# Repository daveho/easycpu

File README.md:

# Easy 8 bit CPU

This is a design for an 8 bit CPU built from 74HC logic chips.

It is totally just for fun.  I may try to complete it at some point but for now it's only at the idea stage.

The [design](design) directory has a block diagram that is probably the most useful document for explaining how the CPU is intended to work.

One potentially useful component that is (probably) ready for use is a passive backplane design, which is in the [backplane2](backplane2) directory.

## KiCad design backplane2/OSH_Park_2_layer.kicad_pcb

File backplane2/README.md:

# Backplane

This is a passive backplane for projects (such as 8 bit micros and
TTL CPUs) where there are lots of parallel bus connections that
would be a pain to wire on breadboards.

The idea is that the project can be built incrementally, with
circuit modules prototyped on a small number of breadboards, and
then permanantly constructed and attached to the backplane.

The eventual finished system then uses the backplane to allow
the various circuit modules to communicate.

Kicad template from <https://github.com/Squantor/templates_kicad/tree/master/OSH_Park_2_layer>

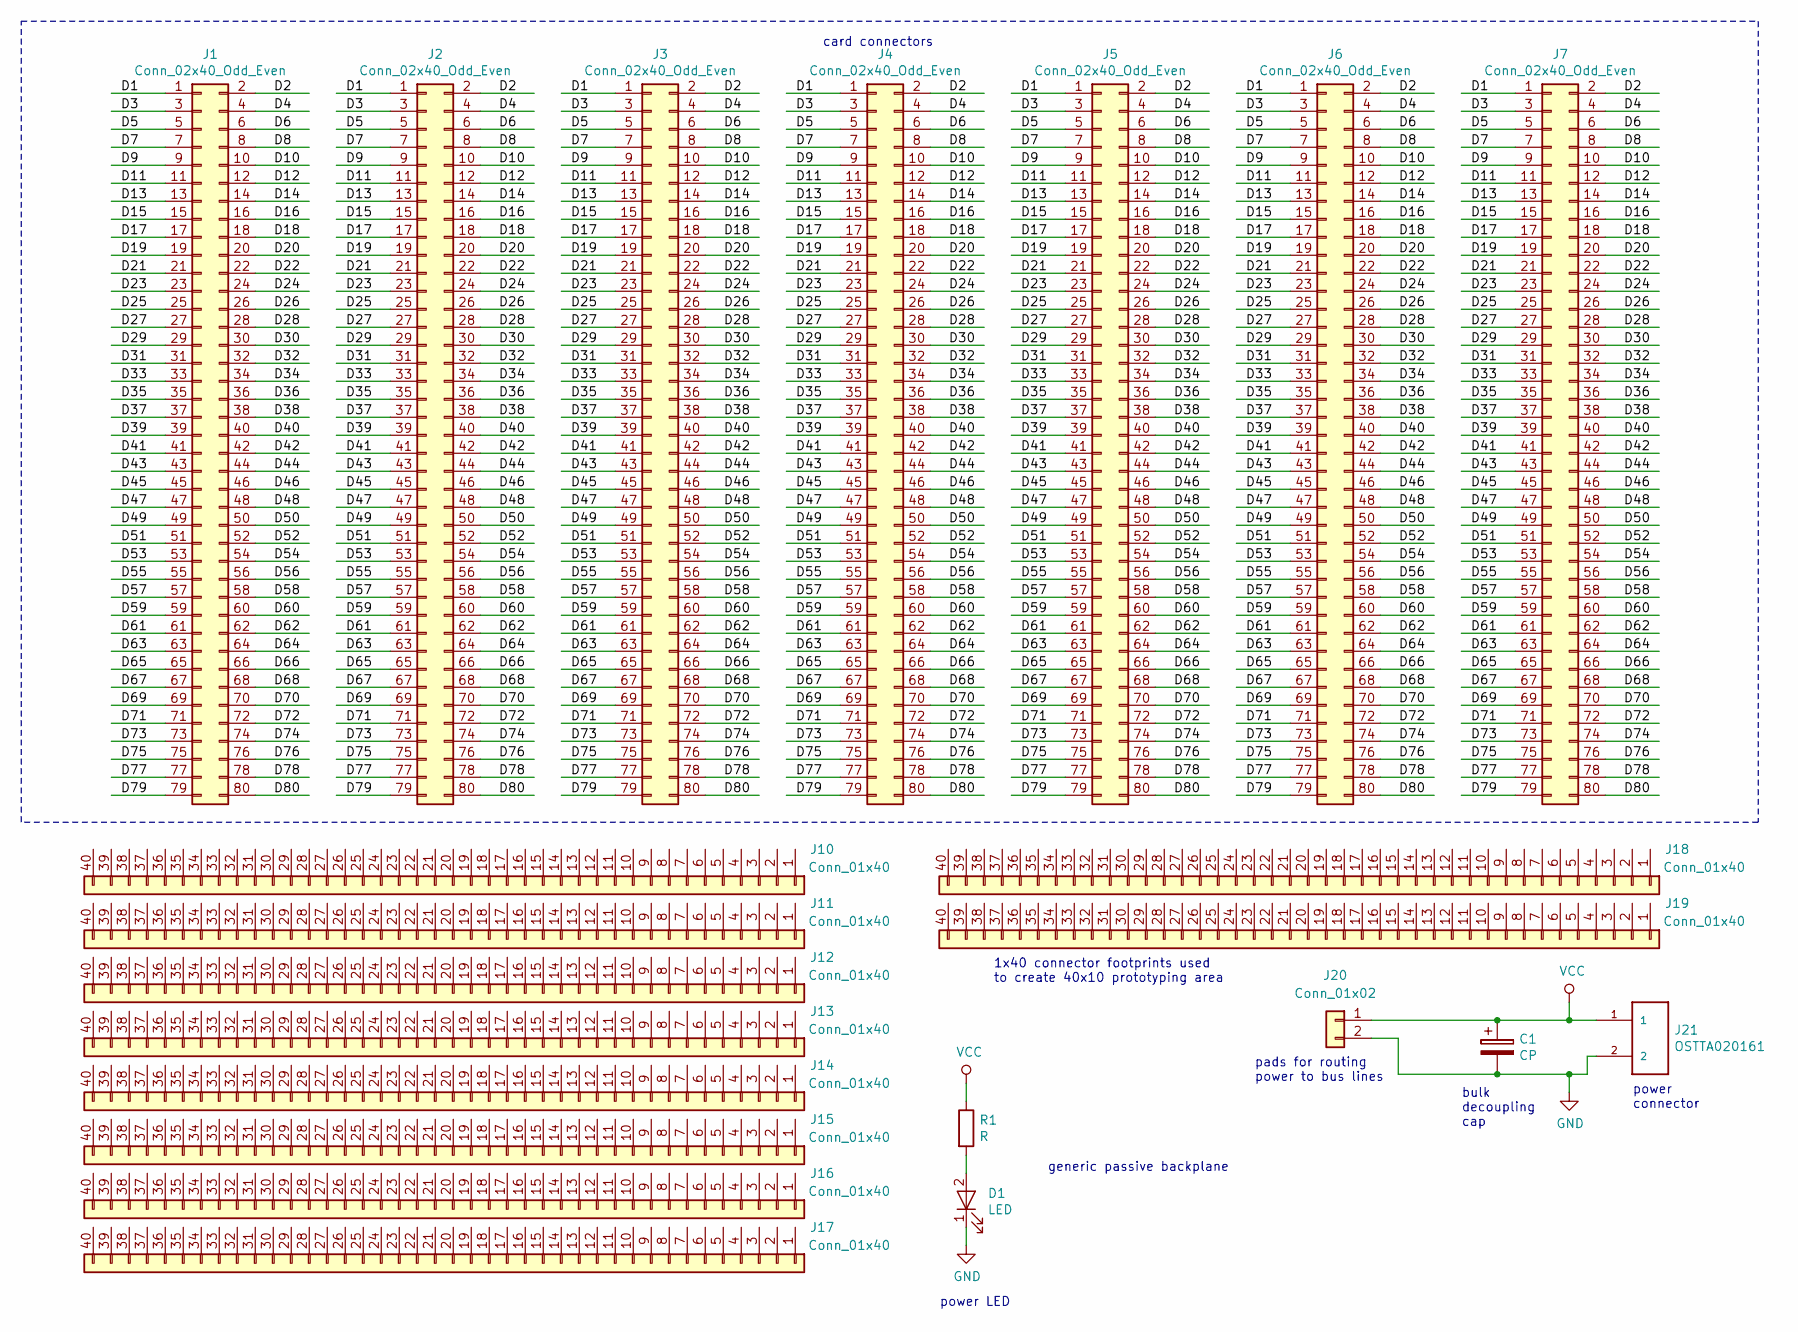
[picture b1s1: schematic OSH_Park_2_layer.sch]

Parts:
C1: CP; CP_Radial_D8.0mm_P2.50mm
D1: LED; LED_D5.0mm
J1, J2, J3, J4, J5, J6, J7: Conn_02x40_Odd_Even; PinHeader_2x40_P2.54mm_Vertical
J10, J11, J12, J13, J14, J15, J16, J17, J18, J19: Conn_01x40; PinHeader_1x40_P2.54mm_Vertical
J20: Conn_01x02; PinHeader_1x02_P2.54mm_Vertical
J21: OSTTA020161; OST_OSTTA020161
R1: R; R_Axial_DIN0204_L3.6mm_D1.6mm_P7.62mm_Horizontal

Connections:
/D1: J1.1, J2.1, J3.1, J4.1, J5.1, J6.1, J7.1
/D2: J1.2, J2.2, J3.2, J4.2, J5.2, J6.2, J7.2
/D3: J1.3, J2.3, J3.3, J4.3, J5.3, J6.3, J7.3
/D4: J1.4, J2.4, J3.4, J4.4, J5.4, J6.4, J7.4
/D5: J1.5, J2.5, J3.5, J4.5, J5.5, J6.5, J7.5
/D6: J1.6, J2.6, J3.6, J4.6, J5.6, J6.6, J7.6
/D7: J1.7, J2.7, J3.7, J4.7, J5.7, J6.7, J7.7
/D8: J1.8, J2.8, J3.8, J4.8, J5.8, J6.8, J7.8
/D9: J1.9, J2.9, J3.9, J4.9, J5.9, J6.9, J7.9
/D10: J1.10, J2.10, J3.10, J4.10, J5.10, J6.10, J7.10
/D11: J1.11, J2.11, J3.11, J4.11, J5.11, J6.11, J7.11
/D12: J1.12, J2.12, J3.12, J4.12, J5.12, J6.12, J7.12
/D13: J1.13, J2.13, J3.13, J4.13, J5.13, J6.13, J7.13
/D14: J1.14, J2.14, J3.14, J4.14, J5.14, J6.14, J7.14
/D15: J1.15, J2.15, J3.15, J4.15, J5.15, J6.15, J7.15
/D16: J1.16, J2.16, J3.16, J4.16, J5.16, J6.16, J7.16
/D17: J1.17, J2.17, J3.17, J4.17, J5.17, J6.17, J7.17
/D18: J1.18, J2.18, J3.18, J4.18, J5.18, J6.18, J7.18
/D19: J1.19, J2.19, J3.19, J4.19, J5.19, J6.19, J7.19
/D20: J1.20, J2.20, J3.20, J4.20, J5.20, J6.20, J7.20
/D21: J1.21, J2.21, J3.21, J4.21, J5.21, J6.21, J7.21
/D22: J1.22, J2.22, J3.22, J4.22, J5.22, J6.22, J7.22
/D23: J1.23, J2.23, J3.23, J4.23, J5.23, J6.23, J7.23
/D24: J1.24, J2.24, J3.24, J4.24, J5.24, J6.24, J7.24
/D25: J1.25, J2.25, J3.25, J4.25, J5.25, J6.25, J7.25
/D26: J1.26, J2.26, J3.26, J4.26, J5.26, J6.26, J7.26
/D27: J1.27, J2.27, J3.27, J4.27, J5.27, J6.27, J7.27
/D28: J1.28, J2.28, J3.28, J4.28, J5.28, J6.28, J7.28
/D29: J1.29, J2.29, J3.29, J4.29, J5.29, J6.29, J7.29
/D30: J1.30, J2.30, J3.30, J4.30, J5.30, J6.30, J7.30
/D31: J1.31, J2.31, J3.31, J4.31, J5.31, J6.31, J7.31
/D32: J1.32, J2.32, J3.32, J4.32, J5.32, J6.32, J7.32
/D33: J1.33, J2.33, J3.33, J4.33, J5.33, J6.33, J7.33
/D34: J1.34, J2.34, J3.34, J4.34, J5.34, J6.34, J7.34
/D35: J1.35, J2.35, J3.35, J4.35, J5.35, J6.35, J7.35
/D36: J1.36, J2.36, J3.36, J4.36, J5.36, J6.36, J7.36
/D37: J1.37, J2.37, J3.37, J4.37, J5.37, J6.37, J7.37
/D38: J1.38, J2.38, J3.38, J4.38, J5.38, J6.38, J7.38
/D39: J1.39, J2.39, J3.39, J4.39, J5.39, J6.39, J7.39
/D40: J1.40, J2.40, J3.40, J4.40, J5.40, J6.40, J7.40
/D41: J1.41, J2.41, J3.41, J4.41, J5.41, J6.41, J7.41
/D42: J1.42, J2.42, J3.42, J4.42, J5.42, J6.42, J7.42
/D43: J1.43, J2.43, J3.43, J4.43, J5.43, J6.43, J7.43
/D44: J1.44, J2.44, J3.44, J4.44, J5.44, J6.44, J7.44
/D45: J1.45, J2.45, J3.45, J4.45, J5.45, J6.45, J7.45
/D46: J1.46, J2.46, J3.46, J4.46, J5.46, J6.46, J7.46
/D47: J1.47, J2.47, J3.47, J4.47, J5.47, J6.47, J7.47
/D48: J1.48, J2.48, J3.48, J4.48, J5.48, J6.48, J7.48
/D49: J1.49, J2.49, J3.49, J4.49, J5.49, J6.49, J7.49
/D50: J1.50, J2.50, J3.50, J4.50, J5.50, J6.50, J7.50
/D51: J1.51, J2.51, J3.51, J4.51, J5.51, J6.51, J7.51
/D52: J1.52, J2.52, J3.52, J4.52, J5.52, J6.52, J7.52
/D53: J1.53, J2.53, J3.53, J4.53, J5.53, J6.53, J7.53
/D54: J1.54, J2.54, J3.54, J4.54, J5.54, J6.54, J7.54
/D55: J1.55, J2.55, J3.55, J4.55, J5.55, J6.55, J7.55
/D56: J1.56, J2.56, J3.56, J4.56, J5.56, J6.56, J7.56
/D57: J1.57, J2.57, J3.57, J4.57, J5.57, J6.57, J7.57
/D58: J1.58, J2.58, J3.58, J4.58, J5.58, J6.58, J7.58
/D59: J1.59, J2.59, J3.59, J4.59, J5.59, J6.59, J7.59
/D60: J1.60, J2.60, J3.60, J4.60, J5.60, J6.60, J7.60
/D61: J1.61, J2.61, J3.61, J4.61, J5.61, J6.61, J7.61
/D62: J1.62, J2.62, J3.62, J4.62, J5.62, J6.62, J7.62
/D63: J1.63, J2.63, J3.63, J4.63, J5.63, J6.63, J7.63
/D64: J1.64, J2.64, J3.64, J4.64, J5.64, J6.64, J7.64
/D65: J1.65, J2.65, J3.65, J4.65, J5.65, J6.65, J7.65
/D66: J1.66, J2.66, J3.66, J4.66, J5.66, J6.66, J7.66
/D67: J1.67, J2.67, J3.67, J4.67, J5.67, J6.67, J7.67
/D68: J1.68, J2.68, J3.68, J4.68, J5.68, J6.68, J7.68
/D69: J1.69, J2.69, J3.69, J4.69, J5.69, J6.69, J7.69
/D70: J1.70, J2.70, J3.70, J4.70, J5.70, J6.70, J7.70
/D71: J1.71, J2.71, J3.71, J4.71, J5.71, J6.71, J7.71
/D72: J1.72, J2.72, J3.72, J4.72, J5.72, J6.72, J7.72
/D73: J1.73, J2.73, J3.73, J4.73, J5.73, J6.73, J7.73
/D74: J1.74, J2.74, J3.74, J4.74, J5.74, J6.74, J7.74
/D75: J1.75, J2.75, J3.75, J4.75, J5.75, J6.75, J7.75
/D76: J1.76, J2.76, J3.76, J4.76, J5.76, J6.76, J7.76
/D77: J1.77, J2.77, J3.77, J4.77, J5.77, J6.77, J7.77
/D78: J1.78, J2.78, J3.78, J4.78, J5.78, J6.78, J7.78
/D79: J1.79, J2.79, J3.79, J4.79, J5.79, J6.79, J7.79
/D80: J1.80, J2.80, J3.80, J4.80, J5.80, J6.80, J7.80
GND: C1.2, D1.1 (K), J20.2, J21.2
unnamed: D1.2 (A), R1.2
VCC: C1.1, J20.1, J21.1, R1.1

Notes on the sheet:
card connectors
1x40 connector footprints used to create 40x10 prototyping area
power connector
generic passive backplane
pads for routing power to bus lines
bulk decoupling cap
power LED

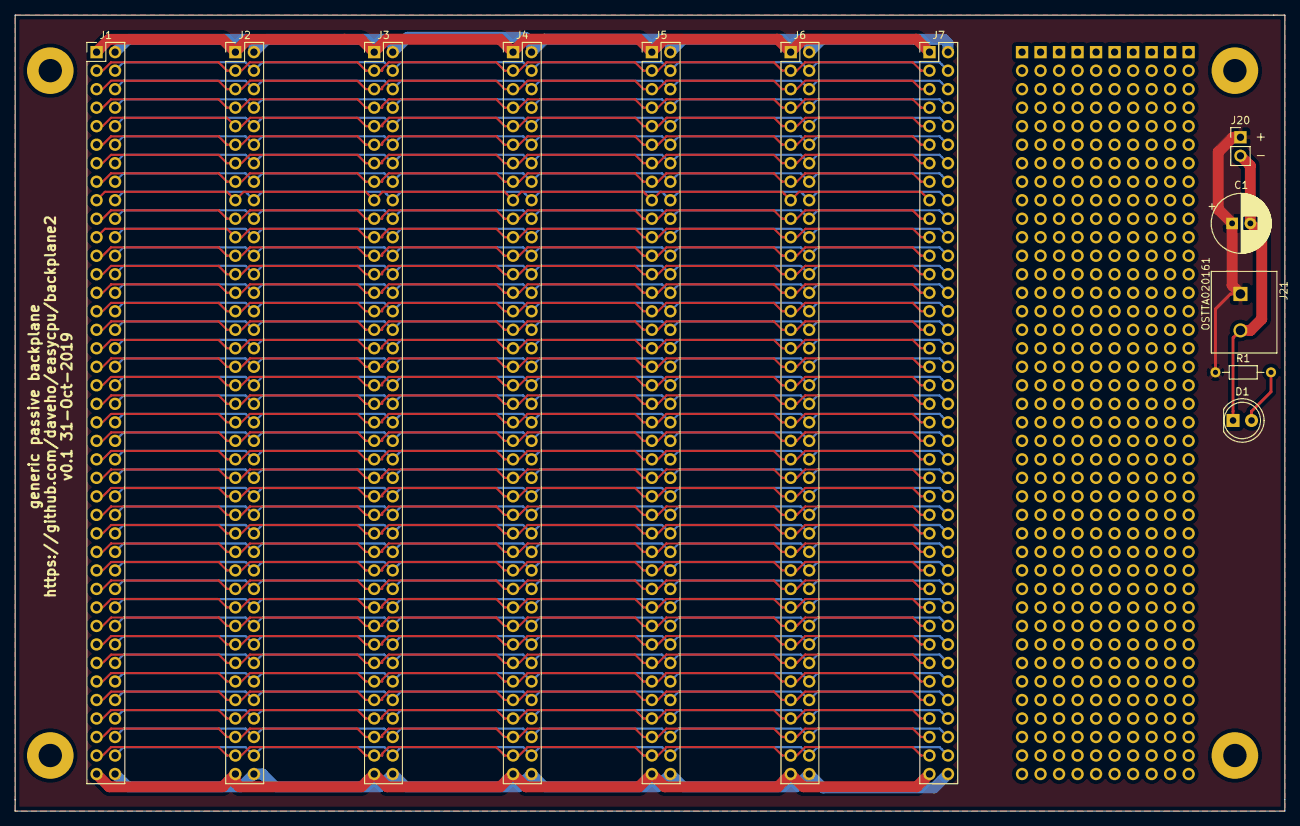
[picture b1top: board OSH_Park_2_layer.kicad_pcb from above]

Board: 2 copper layers, 174.2 x 109.2 mm, 23 parts (0 on the bottom side), 83 nets.

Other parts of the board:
N2: 20190704; Label_version

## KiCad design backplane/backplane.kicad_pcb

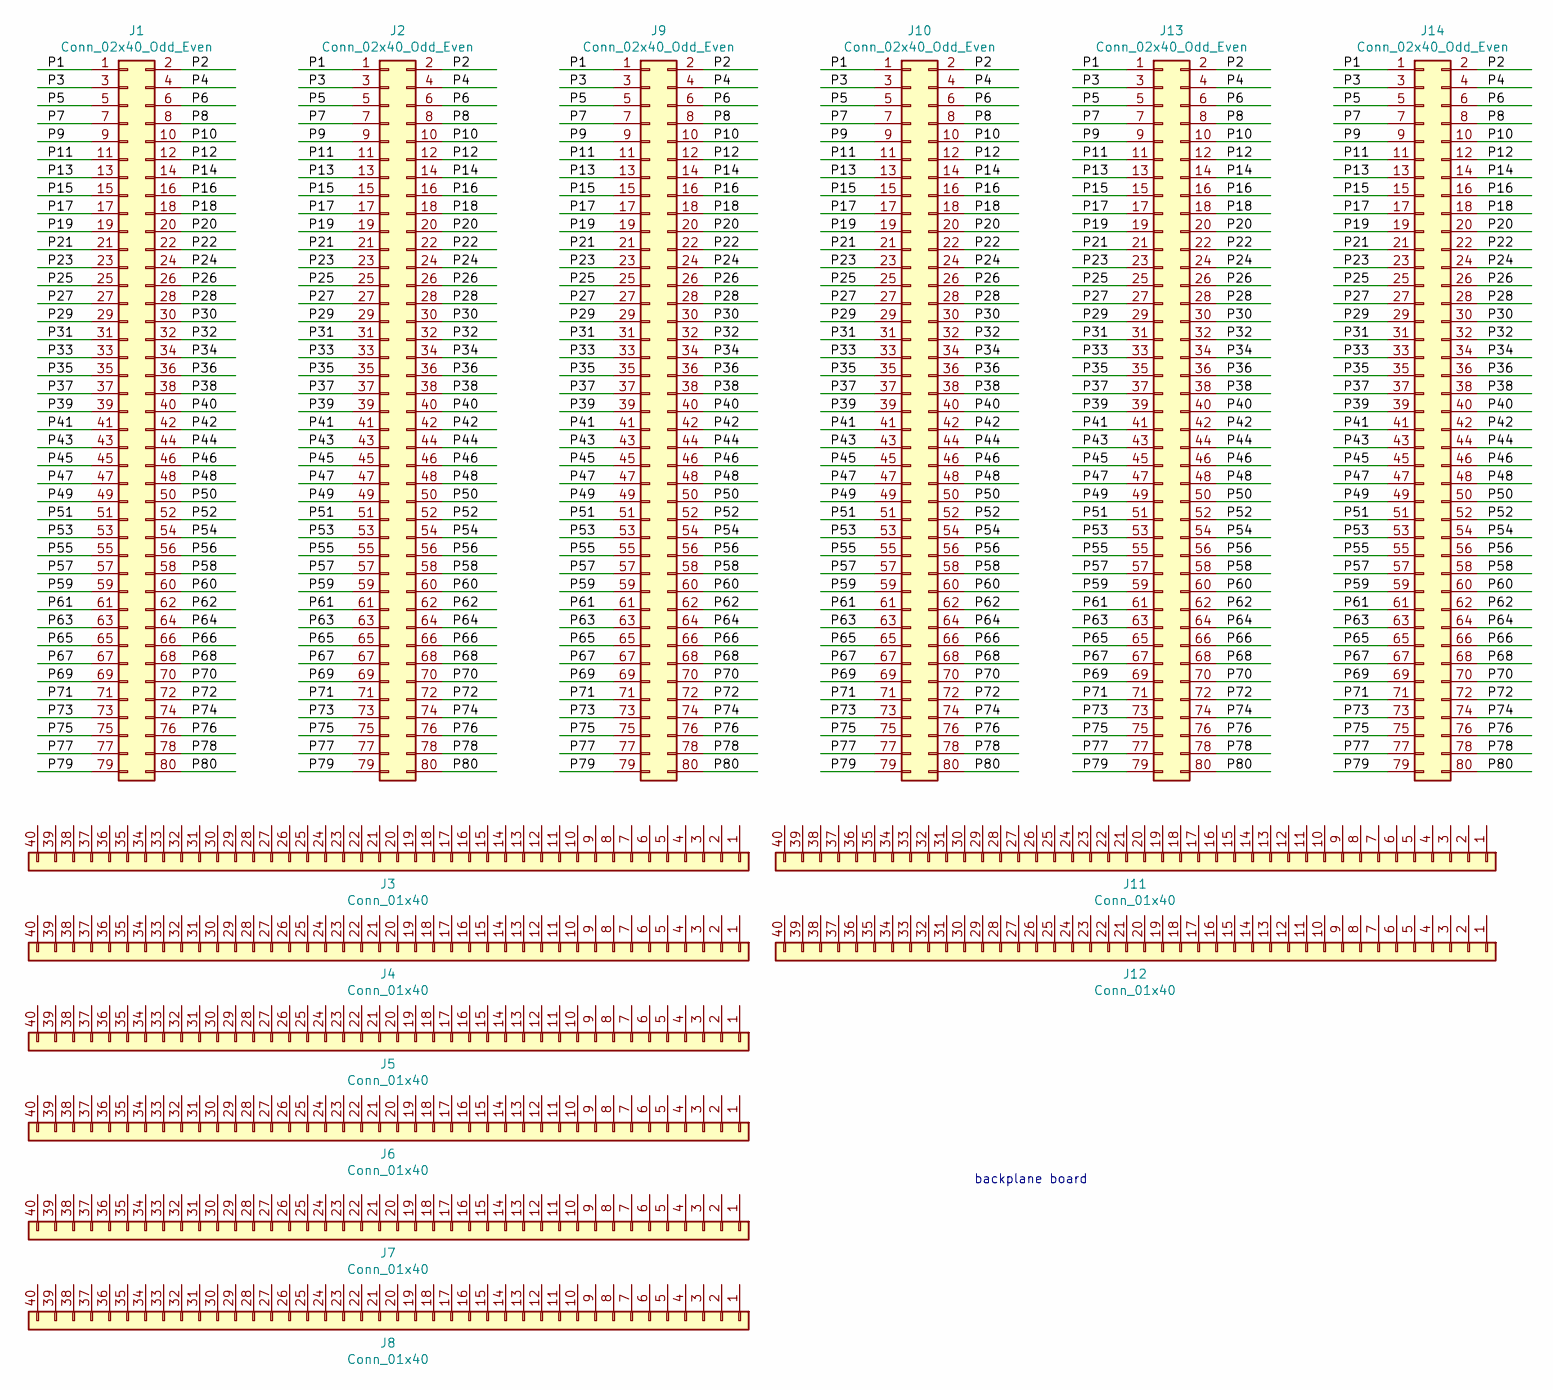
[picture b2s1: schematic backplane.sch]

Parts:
J1, J2, J9, J10, J13, J14: Conn_02x40_Odd_Even; Pin_Header_Straight_2x40_Pitch2.54mm
J3, J4, J5, J6, J7, J8, J11, J12: Conn_01x40; Pin_Header_Straight_1x40_Pitch2.54mm

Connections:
/P1: J1.1, J2.1, J9.1, J10.1, J13.1, J14.1
/P2: J1.2, J2.2, J9.2, J10.2, J13.2, J14.2
/P3: J1.3, J2.3, J9.3, J10.3, J13.3, J14.3
/P4: J1.4, J2.4, J9.4, J10.4, J13.4, J14.4
/P5: J1.5, J2.5, J9.5, J10.5, J13.5, J14.5
/P6: J1.6, J2.6, J9.6, J10.6, J13.6, J14.6
/P7: J1.7, J2.7, J9.7, J10.7, J13.7, J14.7
/P8: J1.8, J2.8, J9.8, J10.8, J13.8, J14.8
/P9: J1.9, J2.9, J9.9, J10.9, J13.9, J14.9
/P10: J1.10, J2.10, J9.10, J10.10, J13.10, J14.10
/P11: J1.11, J2.11, J9.11, J10.11, J13.11, J14.11
/P12: J1.12, J2.12, J9.12, J10.12, J13.12, J14.12
/P13: J1.13, J2.13, J9.13, J10.13, J13.13, J14.13
/P14: J1.14, J2.14, J9.14, J10.14, J13.14, J14.14
/P15: J1.15, J2.15, J9.15, J10.15, J13.15, J14.15
/P16: J1.16, J2.16, J9.16, J10.16, J13.16, J14.16
/P17: J1.17, J2.17, J9.17, J10.17, J13.17, J14.17
/P18: J1.18, J2.18, J9.18, J10.18, J13.18, J14.18
/P19: J1.19, J2.19, J9.19, J10.19, J13.19, J14.19
/P20: J1.20, J2.20, J9.20, J10.20, J13.20, J14.20
/P21: J1.21, J2.21, J9.21, J10.21, J13.21, J14.21
/P22: J1.22, J2.22, J9.22, J10.22, J13.22, J14.22
/P23: J1.23, J2.23, J9.23, J10.23, J13.23, J14.23
/P24: J1.24, J2.24, J9.24, J10.24, J13.24, J14.24
/P25: J1.25, J2.25, J9.25, J10.25, J13.25, J14.25
/P26: J1.26, J2.26, J9.26, J10.26, J13.26, J14.26
/P27: J1.27, J2.27, J9.27, J10.27, J13.27, J14.27
/P28: J1.28, J2.28, J9.28, J10.28, J13.28, J14.28
/P29: J1.29, J2.29, J9.29, J10.29, J13.29, J14.29
/P30: J1.30, J2.30, J9.30, J10.30, J13.30, J14.30
/P31: J1.31, J2.31, J9.31, J10.31, J13.31, J14.31
/P32: J1.32, J2.32, J9.32, J10.32, J13.32, J14.32
/P33: J1.33, J2.33, J9.33, J10.33, J13.33, J14.33
/P34: J1.34, J2.34, J9.34, J10.34, J13.34, J14.34
/P35: J1.35, J2.35, J9.35, J10.35, J13.35, J14.35
/P36: J1.36, J2.36, J9.36, J10.36, J13.36, J14.36
/P37: J1.37, J2.37, J9.37, J10.37, J13.37, J14.37
/P38: J1.38, J2.38, J9.38, J10.38, J13.38, J14.38
/P39: J1.39, J2.39, J9.39, J10.39, J13.39, J14.39
/P40: J1.40, J2.40, J9.40, J10.40, J13.40, J14.40
/P41: J1.41, J2.41, J9.41, J10.41, J13.41, J14.41
/P42: J1.42, J2.42, J9.42, J10.42, J13.42, J14.42
/P43: J1.43, J2.43, J9.43, J10.43, J13.43, J14.43
/P44: J1.44, J2.44, J9.44, J10.44, J13.44, J14.44
/P45: J1.45, J2.45, J9.45, J10.45, J13.45, J14.45
/P46: J1.46, J2.46, J9.46, J10.46, J13.46, J14.46
/P47: J1.47, J2.47, J9.47, J10.47, J13.47, J14.47
/P48: J1.48, J2.48, J9.48, J10.48, J13.48, J14.48
/P49: J1.49, J2.49, J9.49, J10.49, J13.49, J14.49
/P50: J1.50, J2.50, J9.50, J10.50, J13.50, J14.50
/P51: J1.51, J2.51, J9.51, J10.51, J13.51, J14.51
/P52: J1.52, J2.52, J9.52, J10.52, J13.52, J14.52
/P53: J1.53, J2.53, J9.53, J10.53, J13.53, J14.53
/P54: J1.54, J2.54, J9.54, J10.54, J13.54, J14.54
/P55: J1.55, J2.55, J9.55, J10.55, J13.55, J14.55
/P56: J1.56, J2.56, J9.56, J10.56, J13.56, J14.56
/P57: J1.57, J2.57, J9.57, J10.57, J13.57, J14.57
/P58: J1.58, J2.58, J9.58, J10.58, J13.58, J14.58
/P59: J1.59, J2.59, J9.59, J10.59, J13.59, J14.59
/P60: J1.60, J2.60, J9.60, J10.60, J13.60, J14.60
/P61: J1.61, J2.61, J9.61, J10.61, J13.61, J14.61
/P62: J1.62, J2.62, J9.62, J10.62, J13.62, J14.62
/P63: J1.63, J2.63, J9.63, J10.63, J13.63, J14.63
/P64: J1.64, J2.64, J9.64, J10.64, J13.64, J14.64
/P65: J1.65, J2.65, J9.65, J10.65, J13.65, J14.65
/P66: J1.66, J2.66, J9.66, J10.66, J13.66, J14.66
/P67: J1.67, J2.67, J9.67, J10.67, J13.67, J14.67
/P68: J1.68, J2.68, J9.68, J10.68, J13.68, J14.68
/P69: J1.69, J2.69, J9.69, J10.69, J13.69, J14.69
/P70: J1.70, J2.70, J9.70, J10.70, J13.70, J14.70
/P71: J1.71, J2.71, J9.71, J10.71, J13.71, J14.71
/P72: J1.72, J2.72, J9.72, J10.72, J13.72, J14.72
/P73: J1.73, J2.73, J9.73, J10.73, J13.73, J14.73
/P74: J1.74, J2.74, J9.74, J10.74, J13.74, J14.74
/P75: J1.75, J2.75, J9.75, J10.75, J13.75, J14.75
/P76: J1.76, J2.76, J9.76, J10.76, J13.76, J14.76
/P77: J1.77, J2.77, J9.77, J10.77, J13.77, J14.77
/P78: J1.78, J2.78, J9.78, J10.78, J13.78, J14.78
/P79: J1.79, J2.79, J9.79, J10.79, J13.79, J14.79
/P80: J1.80, J2.80, J9.80, J10.80, J13.80, J14.80

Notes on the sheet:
backplane board

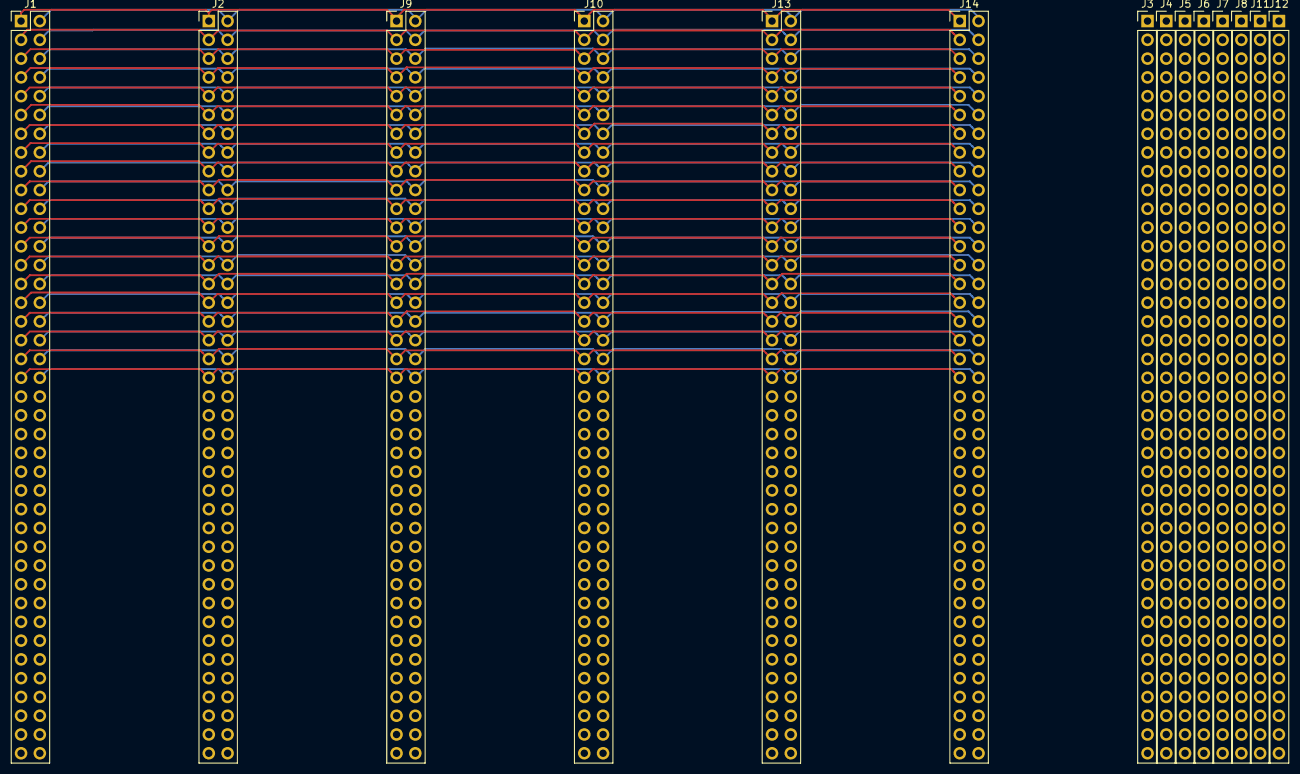
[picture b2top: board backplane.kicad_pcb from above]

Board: 2 copper layers, 14 parts (0 on the bottom side), 80 nets.

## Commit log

2019-10-12 started working on control unit
2019-10-12 annotate control schematic, add other 74HC74 units
2019-10-12 added reset unit, some cleanups of control unit
2019-10-12 control cleanup, generate proper clock for IR load
2019-10-14 start working on ucode and ucode assembler
    I'm focusing on the control unit at the beginning
    since it will be running the show.
2019-10-14 some cleanups/schematic improvements
2019-10-18 create combined clock/reset circuit
    Clock circuit will be removed from control schematic.
2019-10-18 generation of -R/-W signals for mem transactions
2019-10-19 minor tweaks, added sheet pins on main schematic?
2019-10-19 minor gate swap
2019-10-19 some schematic cleanups and descriptive text added
2019-10-19 instructions are one byte, not four
2019-10-19 more signals, actually assemble instructions
2019-10-19 use '273 registers for ucode, initial PC design
    The microcode registers need to be reset to a known
    state on startup. The 74HCT273 is appropriate for this.
    One consequence is that all microcode signals must be
    designed such that a 0 is the correct output for
    coming out of reset: the main thing that needs to
    happen is putting an initial value into the program
2019-10-19 commit cache library
2019-10-20 created a block diagram
    Rather than using a complicated design for the PC, SP,
    and X registers based on up/down counters (e.g, '191),
    allow the result of the address computation to be
    fed back into PC/SP/X. This allows not only increment
    and decrement, but could be the basis for LEA (load
    effective address) instructions.
2019-10-20 minor formatting tweak
2019-10-20 another minor formatting tweak
2019-10-26 create datapath from R0-R3 to AddrIn[7:0]
    This is needed to store 8 bits of a 16 bit address
    for loads to PC (e.g., unconditional jump to an absolute
    16 bit address). Both bytes can't be loaded directly
    from memory, since the first such load would change
    the program counter value.
    Also added IR (Instruction Register).
2019-10-26 added additional control signals
2019-10-26 remove buffer from D to ALo
    Only the high byte of an address will ever be
    loaded from memory via the data bus. The low byte
    of an address is always loaded indirectly from R3.
2019-10-26 comment for jmpAbs instruction
2019-10-26 program counter is now 2x 74HCT574
    Increment is done using the address generation unit,
    and the output of address generation can be optionally
    sent back to the address registers (such as PC)
    via buffers.
    This hugely simplifies the program counter implementation,
    and also makes it easy to provide additional address
2019-10-26 improved layout of OpA bus
2019-10-26 added submodule with all address regs (PC, SP, X)
2019-10-26 diagram cleanup, add more ucode signals to asm
2019-10-26 address registers have only one load input
    Both bytes of the address will always be loaded
    at the same time.
    Also did a few cleanups of the addrReg schematic.
2019-10-26 added schematic for general purpose registers
2019-10-26 simplified GP regs slightly
    An output enable signal for the operand registers
    (R0-R3) is not necessary. The address 0-3 selects
    which one generates output.
2019-10-27 added ALU module
2019-10-27 possible design for passive backplane
2019-10-27 added ALo/AHi output buffers to addrGen unit
2019-10-27 -1 constant outputs don't require hw or control
    They can be generated implicitly with the bus pull-up
    resistors.
2019-10-27 generation of 0 and 1 constant offsets in addrGen
    Also added pullup resistors to the offset bus to ensure
    inputs are valid and also to implicitly generate the
    -1 constant offset.
2019-10-30 backplane project from OSH park template
2019-10-30 added power connector and power LED
2019-10-30 selected component footprints
2019-10-30 working on board design
2019-10-31 routed half of the backplane connections
2019-10-31 completely routed?
2019-10-31 added 4 power distribution traces
    also fixed a couple of unconnected nets
2019-10-31 minor tweak to power LED placement
2019-10-31 updated date (ready to fab now?)
2019-10-31 exported gerber files
2019-11-05 updated README now that repo is public
